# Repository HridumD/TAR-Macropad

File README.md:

# TAR-Macropad
Quick custom Macropad

## Main Features
- 3x3 Macropad
- RGB LEDs
- Rotary Encoder
- Small OLED Screen

## Purpose
- Allow for easy, quick, programmable actions from single button presses of the macropad

## Schematic/PCB

## Casing

## Bill of Materials
- PCB (x1)
- 3D printed parts (x1)
- Cherry MX Style Switches (x9)
- 0.91" OLED Screen (x1)
- Rotary Encoder (x1)
- RGB LEDs (x9)
- Diodes (x9)
- SEED XIAO RP2040 (x1)
- Keycaps (x9)

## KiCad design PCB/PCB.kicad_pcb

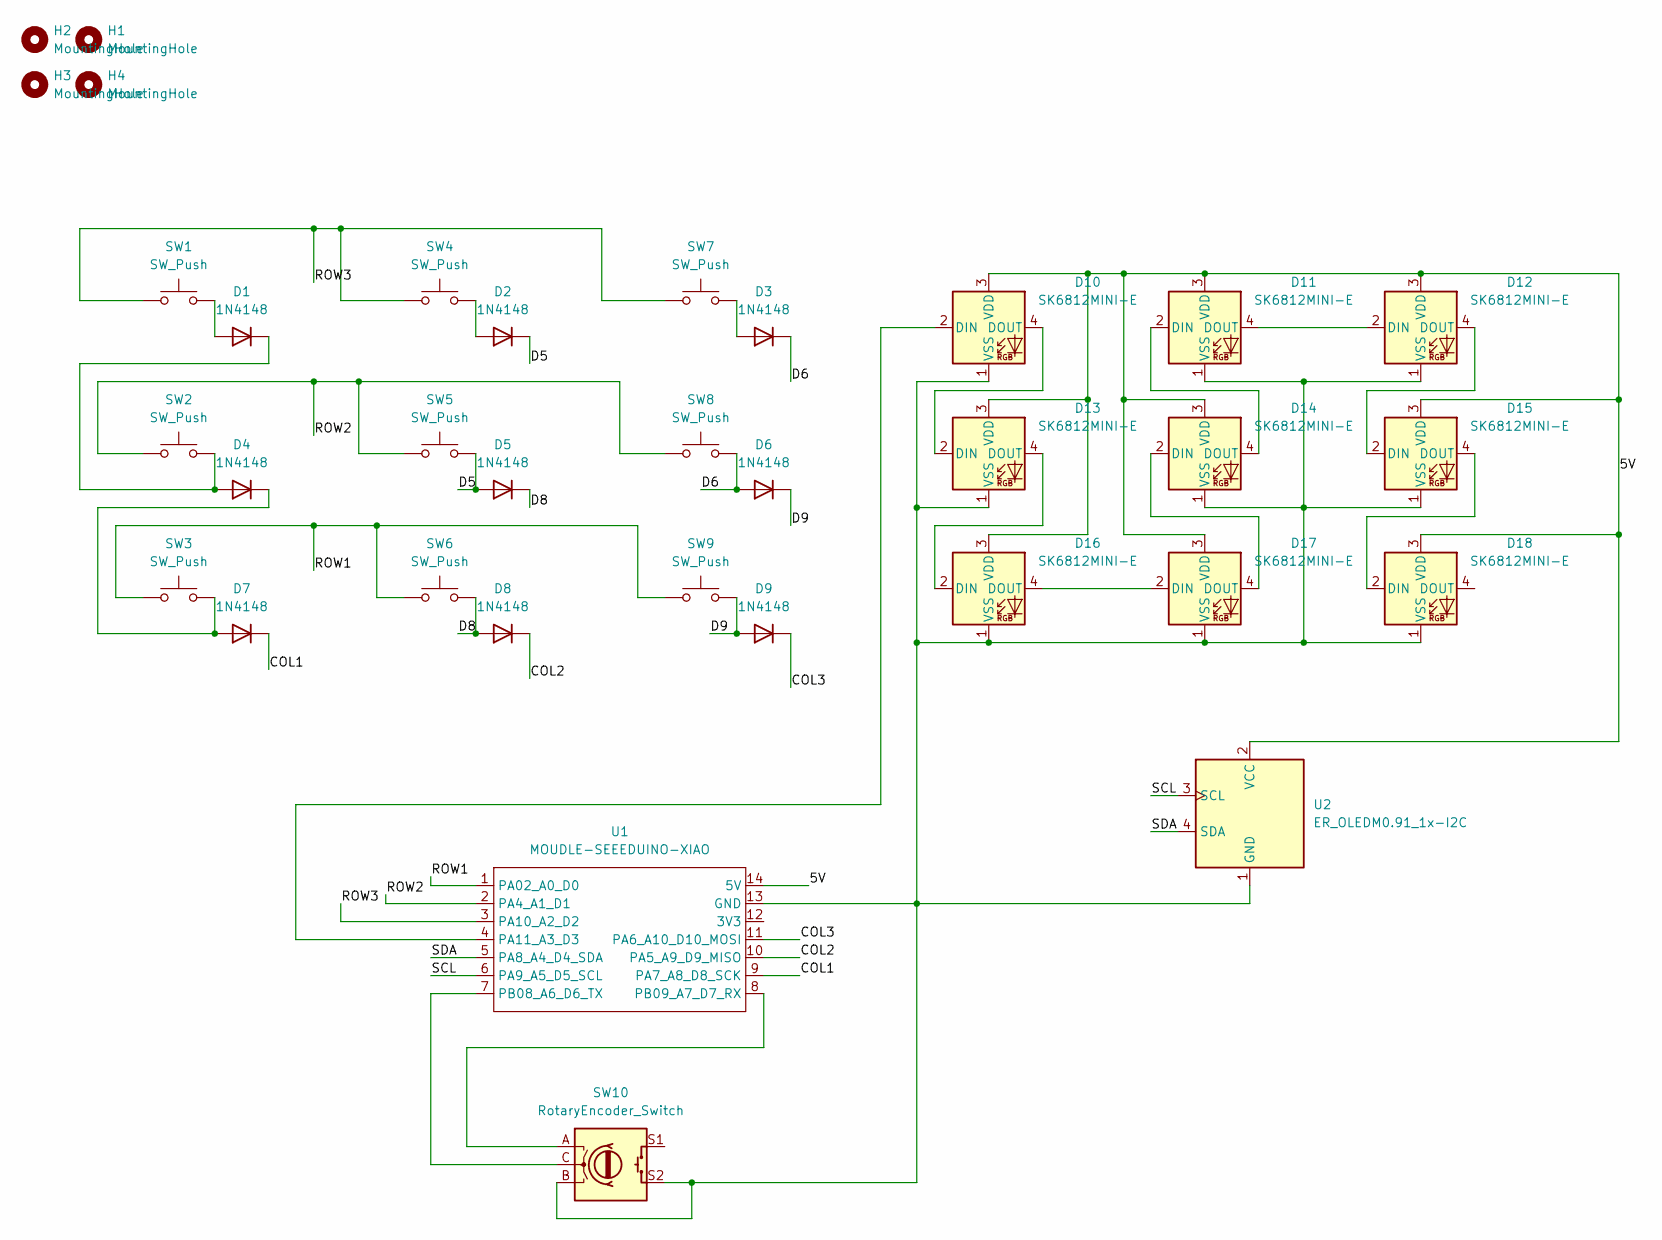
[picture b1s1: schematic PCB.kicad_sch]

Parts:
D1, D2, D3, D4, D5, D6, D7, D8, D9: 1N4148; D_DO-35_SOD27_P7.62mm_Horizontal
D10, D11, D12, D13, D14, D15, D16, D17, D18: SK6812MINI-E; LED_SK6812MINI-E_3.2x2.8mm_P1.5mm_ReverseMount
H1, H2, H3, H4: MountingHole; MountingHole_2.5mm
SW1, SW2, SW3, SW4, SW5, SW6, SW7, SW8, SW9: SW_Push; SW_Cherry_MX_1.00u_PCB
SW10: RotaryEncoder_Switch; RotaryEncoder_Alps_EC11E-Switch_Vertical_H20mm
U1: MOUDLE-SEEEDUINO-XIAO; XIAO-Generic-Hybrid-14P-2.54-21X17.8MM
U2: ER_OLEDM0.91_1x-I2C

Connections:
/5V: D10.3 (VDD), D11.3 (VDD), D12.3 (VDD), D13.3 (VDD), D14.3 (VDD), D15.3 (VDD), D16.3 (VDD), D17.3 (VDD), D18.3 (VDD), U1.14 (5V), U2.2 (VCC)
/COL1: D7.1 (K), U1.9 (PA7_A8_D8_SCK)
/COL2: D8.1 (K), U1.10 (PA5_A9_D9_MISO)
/COL3: D9.1 (K), U1.11 (PA6_A10_D10_MOSI)
/D5: D2.1 (K), D5.2 (A), SW5.2
/D6: D3.1 (K), D6.2 (A), SW8.2
/D8: D5.1 (K), D8.2 (A), SW6.2
/D9: D6.1 (K), D9.2 (A), SW9.2
/ROW1: SW3.1, SW6.1, SW9.1, U1.1 (PA02_A0_D0)
/ROW2: SW2.1, SW5.1, SW8.1, U1.2 (PA4_A1_D1)
/ROW3: SW1.1, SW4.1, SW7.1, U1.3 (PA10_A2_D2)
/SCL: U1.6 (PA9_A5_D5_SCL), U2.3 (SCL)
/SDA: U1.5 (PA8_A4_D4_SDA), U2.4 (SDA)
unnamed: D1.2 (A), SW1.2
unnamed: D1.1 (K), D4.2 (A), SW2.2
unnamed: D2.2 (A), SW4.2
unnamed: D3.2 (A), SW7.2
unnamed: D4.1 (K), D7.2 (A), SW3.2
unnamed: D10.2 (DIN), U1.4 (PA11_A3_D3)
unnamed: D10.4 (DOUT), D13.2 (DIN)
unnamed: D10.1 (VSS), D11.1 (VSS), D12.1 (VSS), D13.1 (VSS), D14.1 (VSS), D15.1 (VSS), D16.1 (VSS), D17.1 (VSS), D18.1 (VSS), SW10.B, SW10.S2, U1.13 (GND), U2.1 (GND)
unnamed: D11.2 (DIN), D14.4 (DOUT)
unnamed: D11.4 (DOUT), D12.2 (DIN)
unnamed: D12.4 (DOUT), D15.2 (DIN)
unnamed: D13.4 (DOUT), D16.2 (DIN)
unnamed: D14.2 (DIN), D17.4 (DOUT)
unnamed: D15.4 (DOUT), D18.2 (DIN)
unnamed: D16.4 (DOUT), D17.2 (DIN)
unnamed: SW10.C, U1.7 (PB08_A6_D6_TX)
unnamed: SW10.A, U1.8 (PB09_A7_D7_RX)

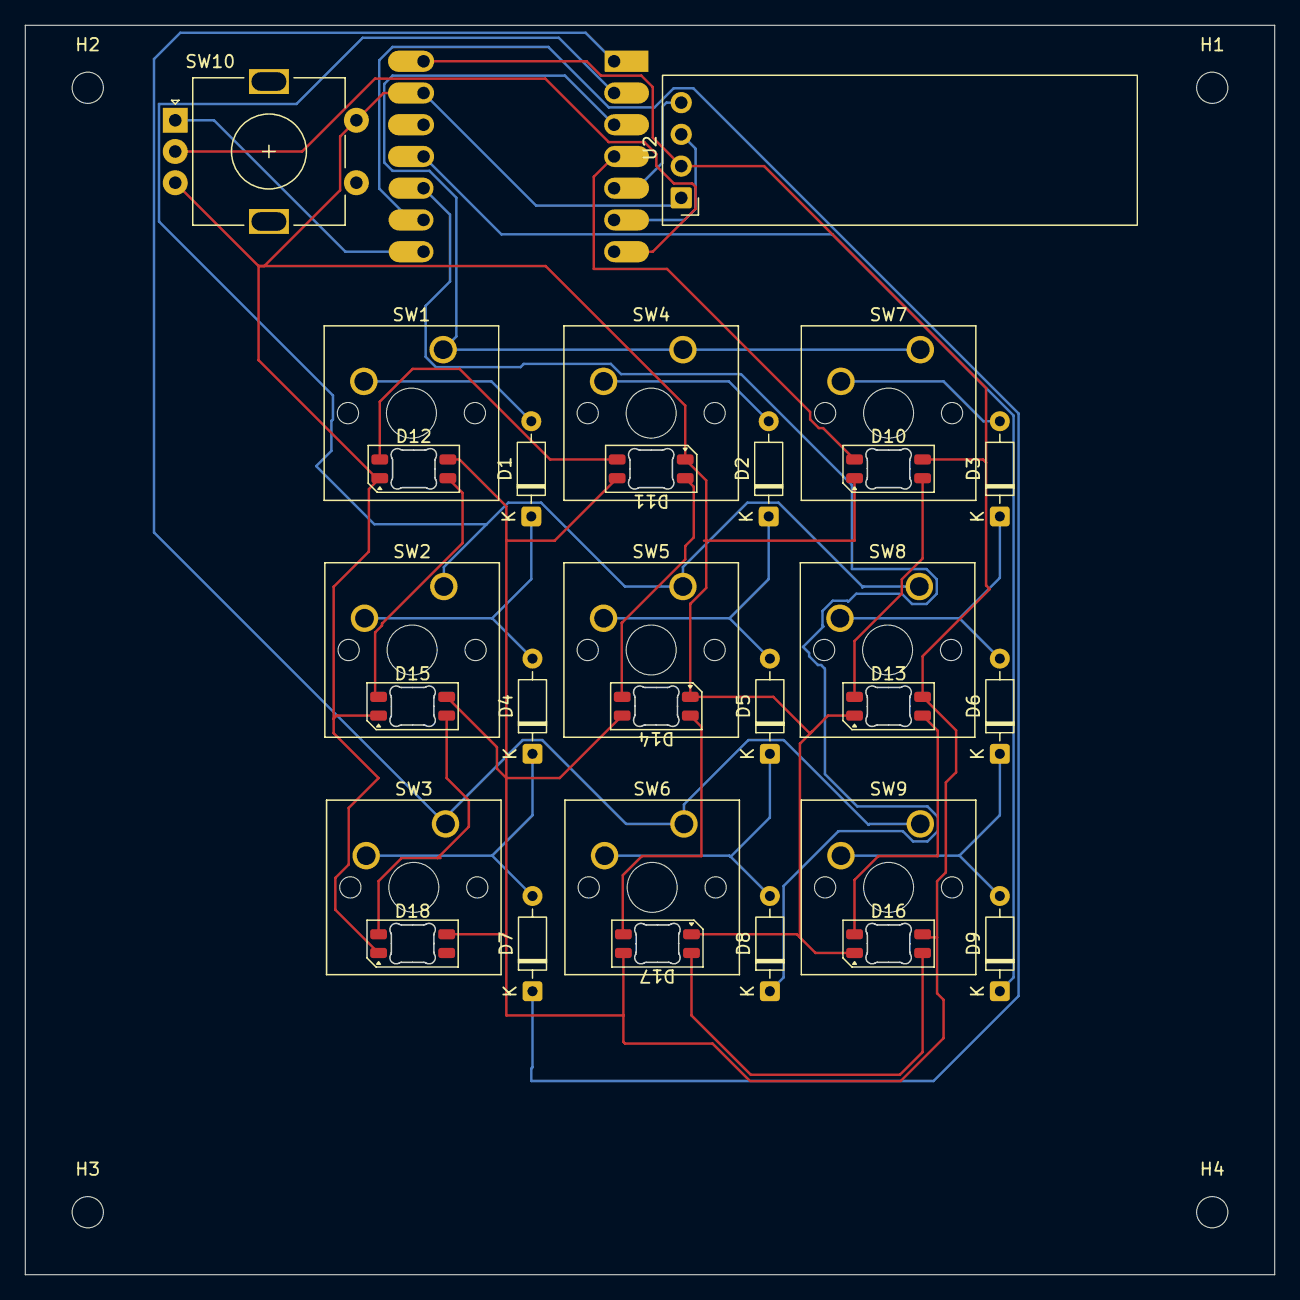
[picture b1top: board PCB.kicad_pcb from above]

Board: 2 copper layers, 99.9 x 99.9 mm, 34 parts (1 on the bottom side), 30 nets.

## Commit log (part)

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2026-06-05 Added PCB for Macropad
2026-06-19 Created PCB and CAD for casing
    Also slightly changed positioning and size of PCB
2026-06-25 Updated READMe and organized Files
2026-06-28 Added BOM.xlsx
